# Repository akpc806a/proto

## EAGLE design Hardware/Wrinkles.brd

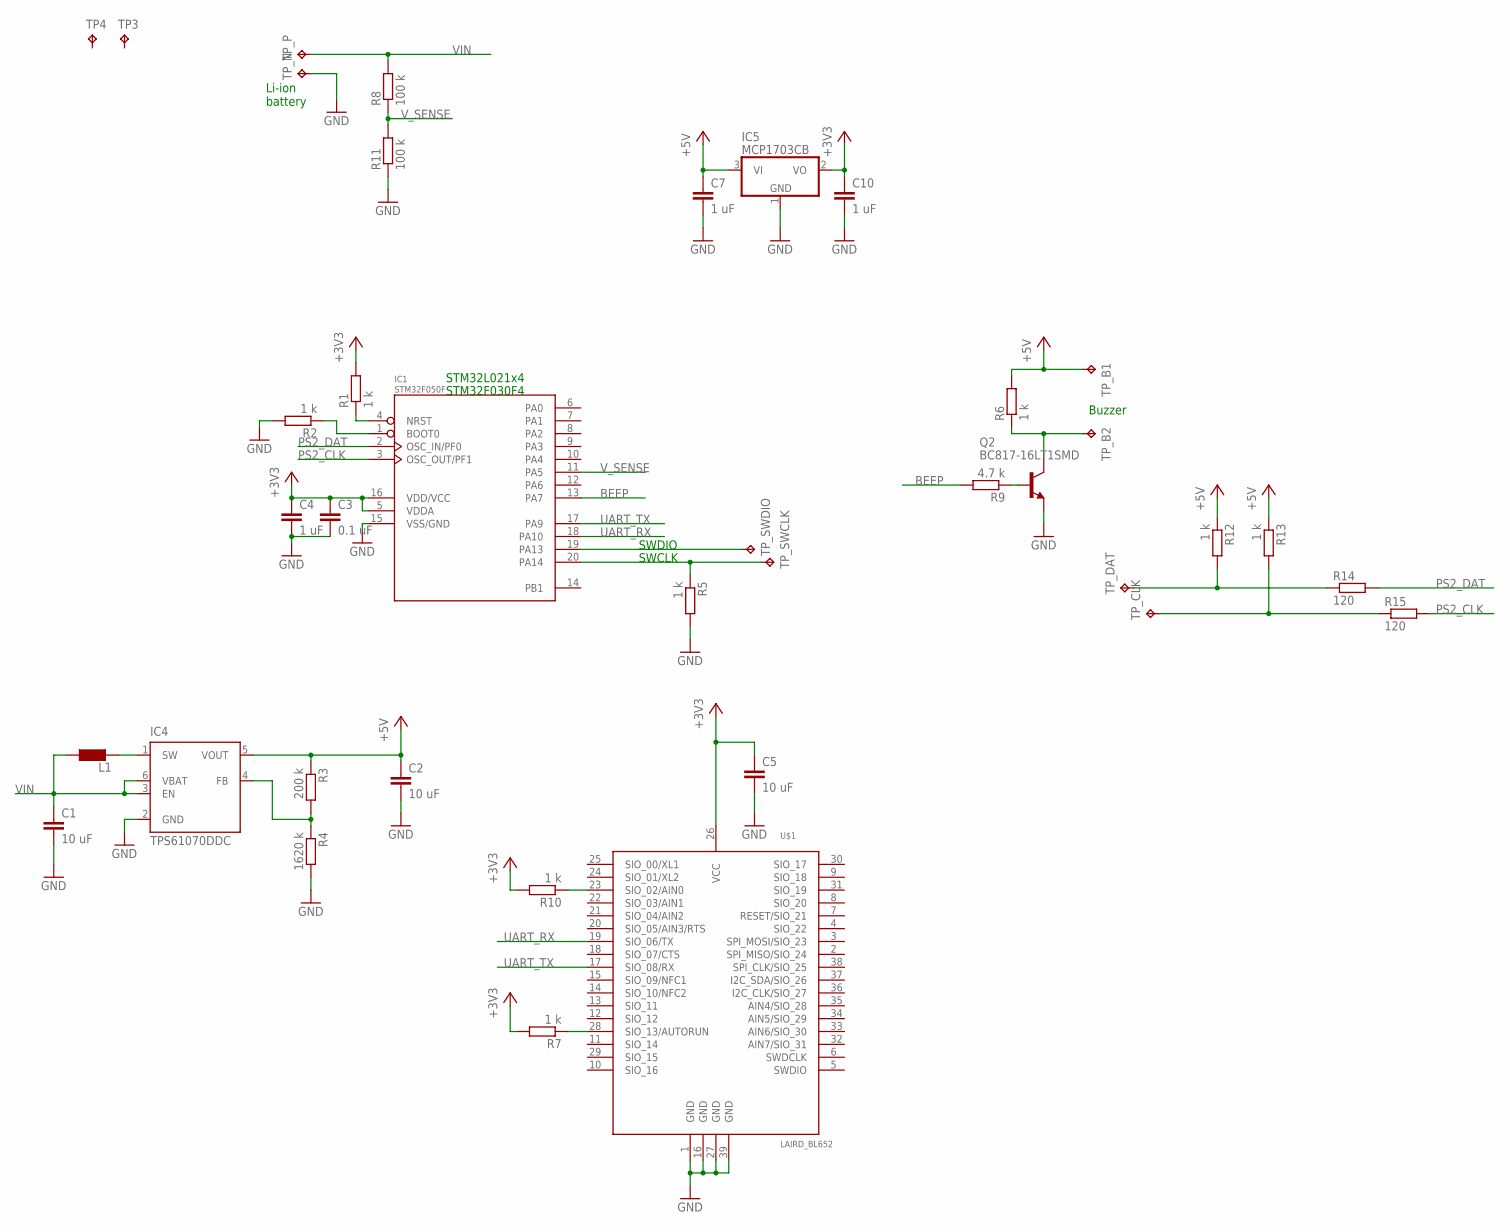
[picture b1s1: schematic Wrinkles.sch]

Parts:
C1, C2, C5: 10 uF; C0603
C3: 0.1 uF; C0402
C4, C7, C10: 1 uF; C0402
IC1: STM32F050F; TSSOP20
IC4: TPS61070DDC; TSOT23-6_DDC
IC5: MCP1703CB; SOT23
L1: LL5038P; L5038P
Q2: BC817-16LT1SMD; SOT23-BEC
R1, R2, R5, R6, R7, R10, R12, R13: 1 k; R0402
R3: 200 k; R0603
R4: 1620 k; R0603
R8, R11: 100 k; R0402
R9: 4.7 k; R0402
R14, R15: 120; R0402
TP3, TP4: TPPAD1-13; P1-13
TP_B1, TP_B2: TPPAD1-13; P1-13
TP_CLK: TPTP10SQ; TP10SQ
TP_DAT: TPTP10SQ; TP10SQ
TP_N: TPPAD1-13; P1-13
TP_P: TPPAD1-13; P1-13
TP_SWCLK: TPTP10SQ; TP10SQ
TP_SWDIO: TPTP10SQ; TP10SQ
U$1: LAIRD_BL652; BL652

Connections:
+3V3: C3.1, C4.1, C5.1, C10.1, IC1.5 (VDDA), IC1.16 (VDD/VCC), IC5.2 (VO), R1.2, R7.2, R10.2, U$1.26 (VCC)
+5V: C2.1, C7.1, IC4.5 (VOUT), IC5.3 (VI), R3.1, R6.2, R12.1, R13.1, TP_B1.TP
BEEP: IC1.13 (PA7), R9.2
GND: C1.2, C2.2, C3.2, C4.2, C5.2, C7.2, C10.2, IC1.15 (VSS/GND), IC4.2 (GND), IC5.1 (GND), Q2.E, R2.2, R4.2, R5.2, R11.1, TP_N.TP, U$1.1 (GND), U$1.16 (GND), U$1.27 (GND), U$1.39 (GND)
unnamed: R7.1, U$1.28 (SIO_13/AUTORUN)
unnamed: R10.1, U$1.23 (SIO_02/AIN0)
unnamed: IC1.4 (NRST), R1.1
unnamed: IC1.1 (BOOT0), R2.1
unnamed: IC4.1 (SW), L1.2
unnamed: IC1.19 (PA13), TP_SWDIO.TP
unnamed: IC1.20 (PA14), R5.1, TP_SWCLK.TP
unnamed: R12.2, R14.1, TP_DAT.TP
unnamed: R13.2, R15.1, TP_CLK.TP
unnamed: IC4.4 (FB), R3.2, R4.1
unnamed: Q2.B, R9.1
unnamed: Q2.C, R6.1, TP_B2.TP
PS2_CLK: IC1.3 (OSC_OUT/PF1), R15.2
PS2_DAT: IC1.2 (OSC_IN/PF0), R14.2
UART_RX: IC1.18 (PA10), U$1.19 (SIO_06/TX)
UART_TX: IC1.17 (PA9), U$1.17 (SIO_08/RX)
VIN: C1.1, IC4.3 (EN), IC4.6 (VBAT), L1.1, R8.2, TP_P.TP
V_SENSE: IC1.11 (PA5), R8.1, R11.2

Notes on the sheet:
SWDIO
SWCLK
STM32F030F4
Li-ion battery
Buzzer
STM32L021x4

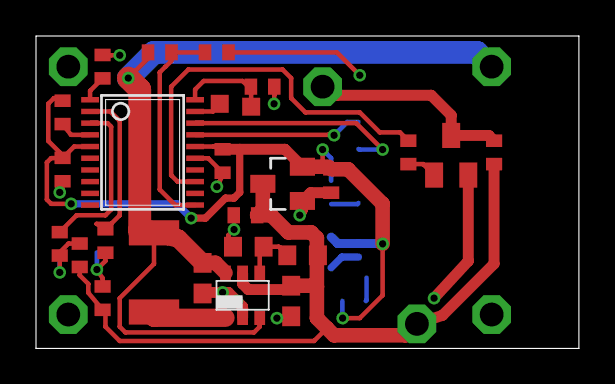
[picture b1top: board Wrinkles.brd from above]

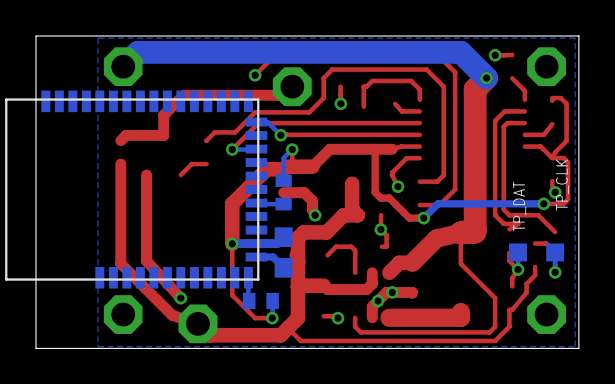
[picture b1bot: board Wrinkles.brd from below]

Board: 2 copper layers, 30.2 x 17.4 mm, 38 parts (6 on the bottom side), 22 nets.

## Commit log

2017-03-14 initial commit (hardware and firmware prototype)
